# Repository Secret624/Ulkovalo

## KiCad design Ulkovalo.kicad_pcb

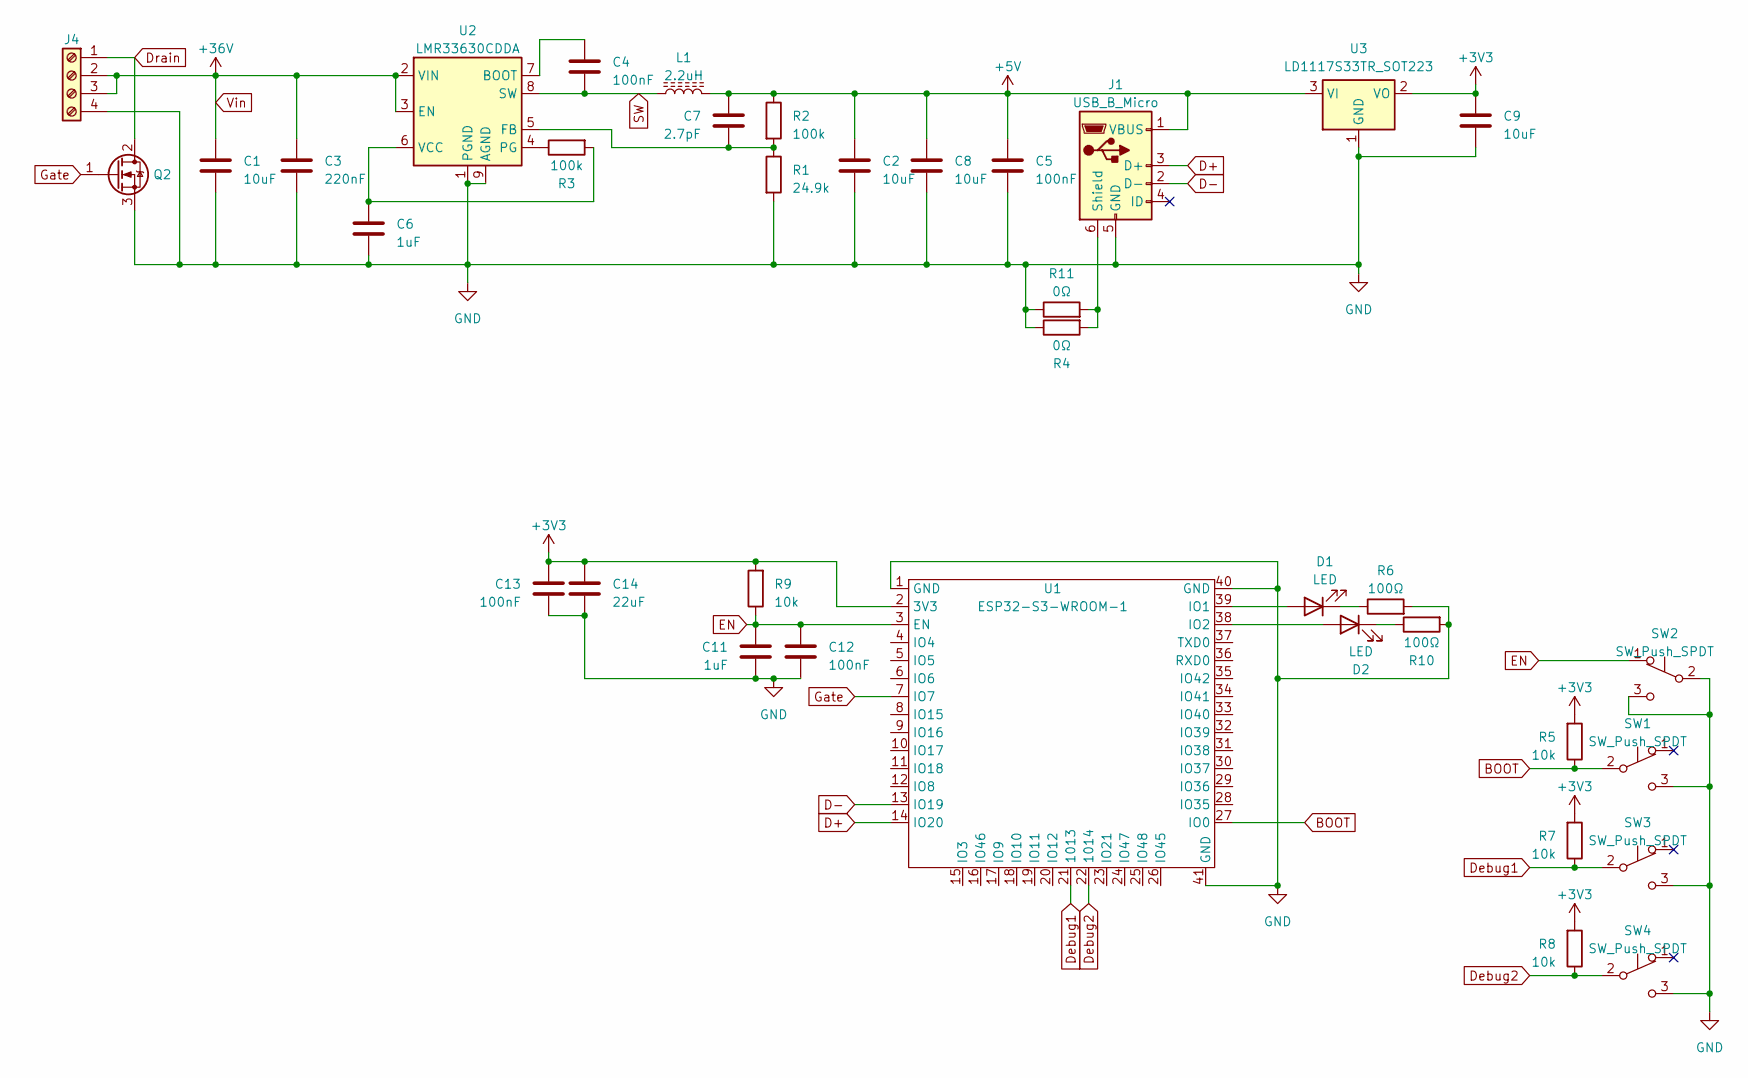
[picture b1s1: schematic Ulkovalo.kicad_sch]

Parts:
C1: 10uF; C_1210_3225Metric_Pad1.33x2.70mm_HandSolder; MFR# C3225X7R1H106M250AC; LCSC# C77102
C2, C8, C9: 10uF; C_1206_3216Metric_Pad1.33x1.80mm_HandSolder; MFR# GRM31CR71E106KA12K; LCSC# C882506
C3: 220nF; C_0805_2012Metric_Pad1.18x1.45mm_HandSolder; MFR# C2012X7R1H224K125AA; LCSC# C163697
C4, C5: 100nF; C_0805_2012Metric_Pad1.18x1.45mm_HandSolder; MFR# 885012207045; LCSC# C519980
C6: 1uF; C_0805_2012Metric_Pad1.18x1.45mm_HandSolder; MFR# CC0805KKX5R6BB105; LCSC# C408907
C7: 2.7pF; C_0805_2012Metric_Pad1.18x1.45mm_HandSolder; MFR# CC0805CRNPO9BN2R7; LCSC# C519936
C11: 1uF; C_0805_2012Metric_Pad1.18x1.45mm_HandSolder; MFR# CL21B105KAFNNNG; LCSC# C215803
C12, C13: 100nF; C_0805_2012Metric_Pad1.18x1.45mm_HandSolder; MFR# CL21B104MACNNNC; LCSC# C476766
C14: 22uF; C_0805_2012Metric_Pad1.18x1.45mm_HandSolder; MFR# CL21A226MOQNNNE; LCSC# C380338
D1, D2: LED; LED_0805_2012Metric_Pad1.15x1.40mm_HandSolder; MFR# 150080RS75000; LCSC# C84256
J1: USB_B_Micro; USB_Micro-B_Wuerth_614105150721_Vertical_CircularHoles; MFR# 614105150721; LCSC# C456007
J4: Screw_Terminal_01x04; TerminalBlock_TE_282834-4_1x04_P2.54mm_Horizontal; MFR# 282834-4
L1: 2.2uH; L_TDK_VLS6045EX_VLS6045AF; MFR# VLS6045EX-2R2N; LCSC# C404501
Q2: Q_NMOS_GDS; TO-252-2; MFR# DMN4030LK3; LCSC# C464112
R1: 24.9k; R_0805_2012Metric_Pad1.20x1.40mm_HandSolder; MFR# AC0805FR-0724K9L; LCSC# C228658
R2, R3: 100k; R_0805_2012Metric_Pad1.20x1.40mm_HandSolder; MFR# RC0805FR-10100KL; LCSC# C2907293
R4, R11: 0Ω; R_0805_2012Metric_Pad1.20x1.40mm_HandSolder; MFR# RC0805FR-130RL; LCSC# C112378
R5, R7, R8, R9: 10k; R_0805_2012Metric_Pad1.20x1.40mm_HandSolder; MFR# AC0805FR-0710KL; LCSC# C17414
R6, R10: 100Ω; R_0805_2012Metric_Pad1.20x1.40mm_HandSolder; MFR# CRCW0805100RFKEB; LCSC# C3016626
SW1, SW2, SW3, SW4: SW_Push_SPDT; G-Switch-MK-12C02-G020; LCSC# C963206
U1: ESP32-S3-WROOM-1; MFR# ESP32-S3-WROOM-1-N4; LCSC# C2913197
U2: LMR33630CDDA; Texas_HSOP-8-1EP_3.9x4.9mm_P1.27mm; MFR# LMR33630CDDA; LCSC# C841384
U3: LD1117S33TR_SOT223; SOT-223-3_TabPin2; LCSC# C86781

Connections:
+3V3: C9.1, C13.1, C14.1, R5.2, R7.2, R8.2, R9.2, U1.2 (3V3), U3.2 (VO)
+5V: C2.1, C5.1, C7.1, C8.1, J1.1 (VBUS), L1.2, R2.1, U3.3 (VI)
BOOT: R5.1, SW1.2 (B), U1.27 (IO0)
D+: J1.3 (D+), U1.14 (IO20)
D-: J1.2 (D-), U1.13 (IO19)
Debug1: R7.1, SW3.2 (B), U1.21 (1013)
Debug2: R8.1, SW4.2 (B), U1.22 (1014)
Drain: J4.1, Q2.2 (D)
EN: C11.1, C12.1, R9.1, SW2.1 (A), U1.3 (EN)
GND: C1.2, C2.2, C3.2, C5.2, C6.2, C8.2, C9.2, C11.2, C12.2, C13.2, C14.2, J1.5 (GND), J4.4, Q2.3 (S), R1.2, R4.1, R6.2, R10.2, R11.1, SW1.3 (C), SW2.2 (B), SW2.3 (C), SW3.3 (C), SW4.3 (C), U1.1 (GND), U1.40 (GND), U1.41 (GND), U2.1 (PGND), U2.9 (AGND), U3.1 (GND)
Gate: Q2.1 (G), U1.7 (IO7)
unnamed: D1.2 (A), U1.39 (IO1)
unnamed: D1.1 (K), R6.1
unnamed: D2.2 (A), U1.38 (IO2)
unnamed: D2.1 (K), R10.1
unnamed: J1.6 (Shield), R4.2, R11.2
unnamed: C4.1, U2.7 (BOOT)
unnamed: C7.2, R1.1, R2.2, U2.5 (FB)
unnamed: R3.1, U2.4 (PG)
unnamed: C6.1, R3.2, U2.6 (VCC)
SW: C4.2, L1.1, U2.8 (SW)
Vin: C1.1, C3.1, J4.2, J4.3, U2.2 (VIN), U2.3 (EN)

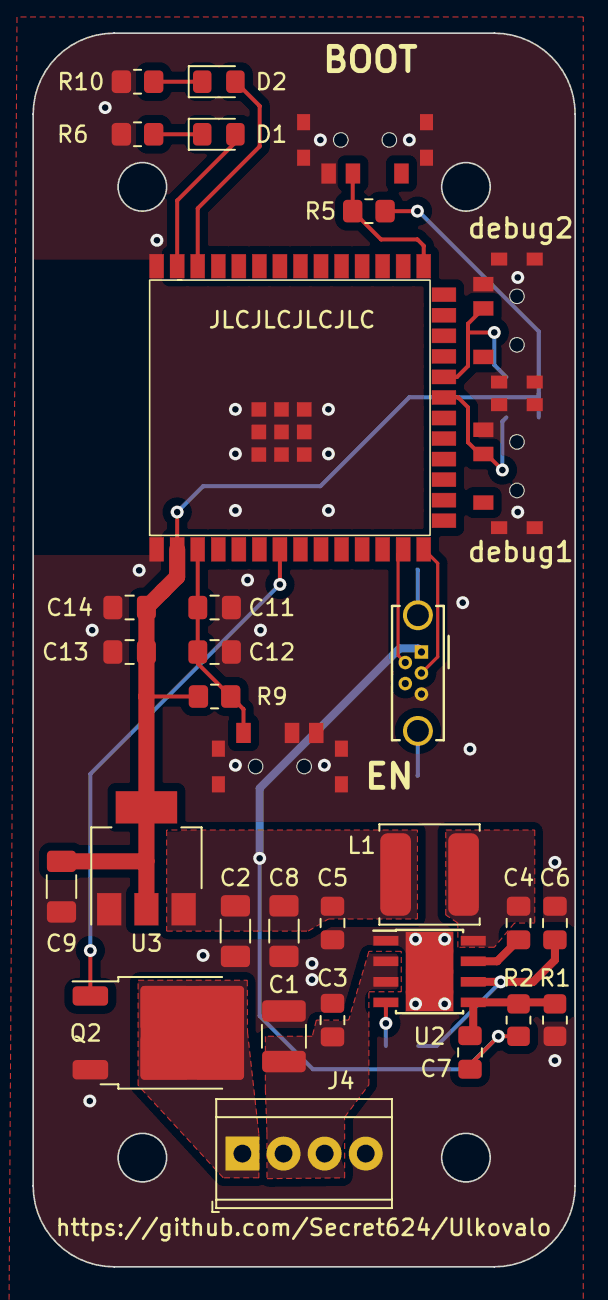
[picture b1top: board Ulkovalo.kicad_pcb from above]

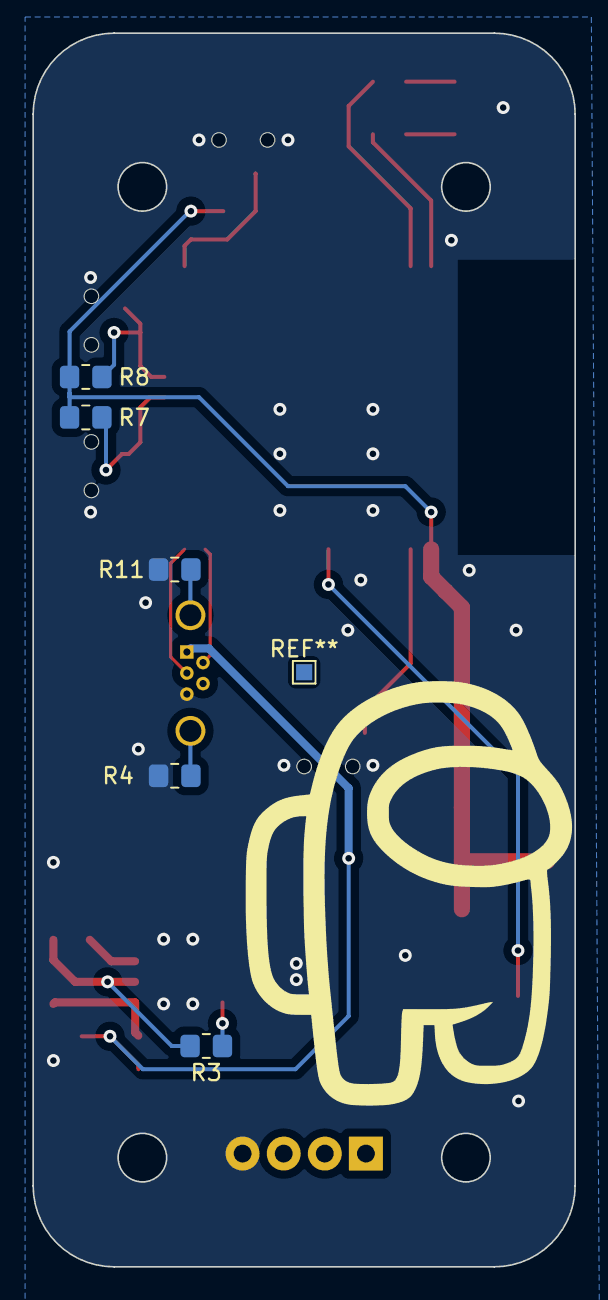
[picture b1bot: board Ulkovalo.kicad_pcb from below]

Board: 2 copper layers, 33.5 x 76.2 mm, 37 parts (5 on the bottom side), 22 nets.
